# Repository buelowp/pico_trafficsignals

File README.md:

# Pi Pico Traffic Signals

Imitate road traffic signals for common anode RYB traffic signals used in model railroads.

This is a common anode solution and includes the PCB design in Eagle.

To build and run this, see the SDK instructions

https://github.com/raspberrypi/pico-sdk

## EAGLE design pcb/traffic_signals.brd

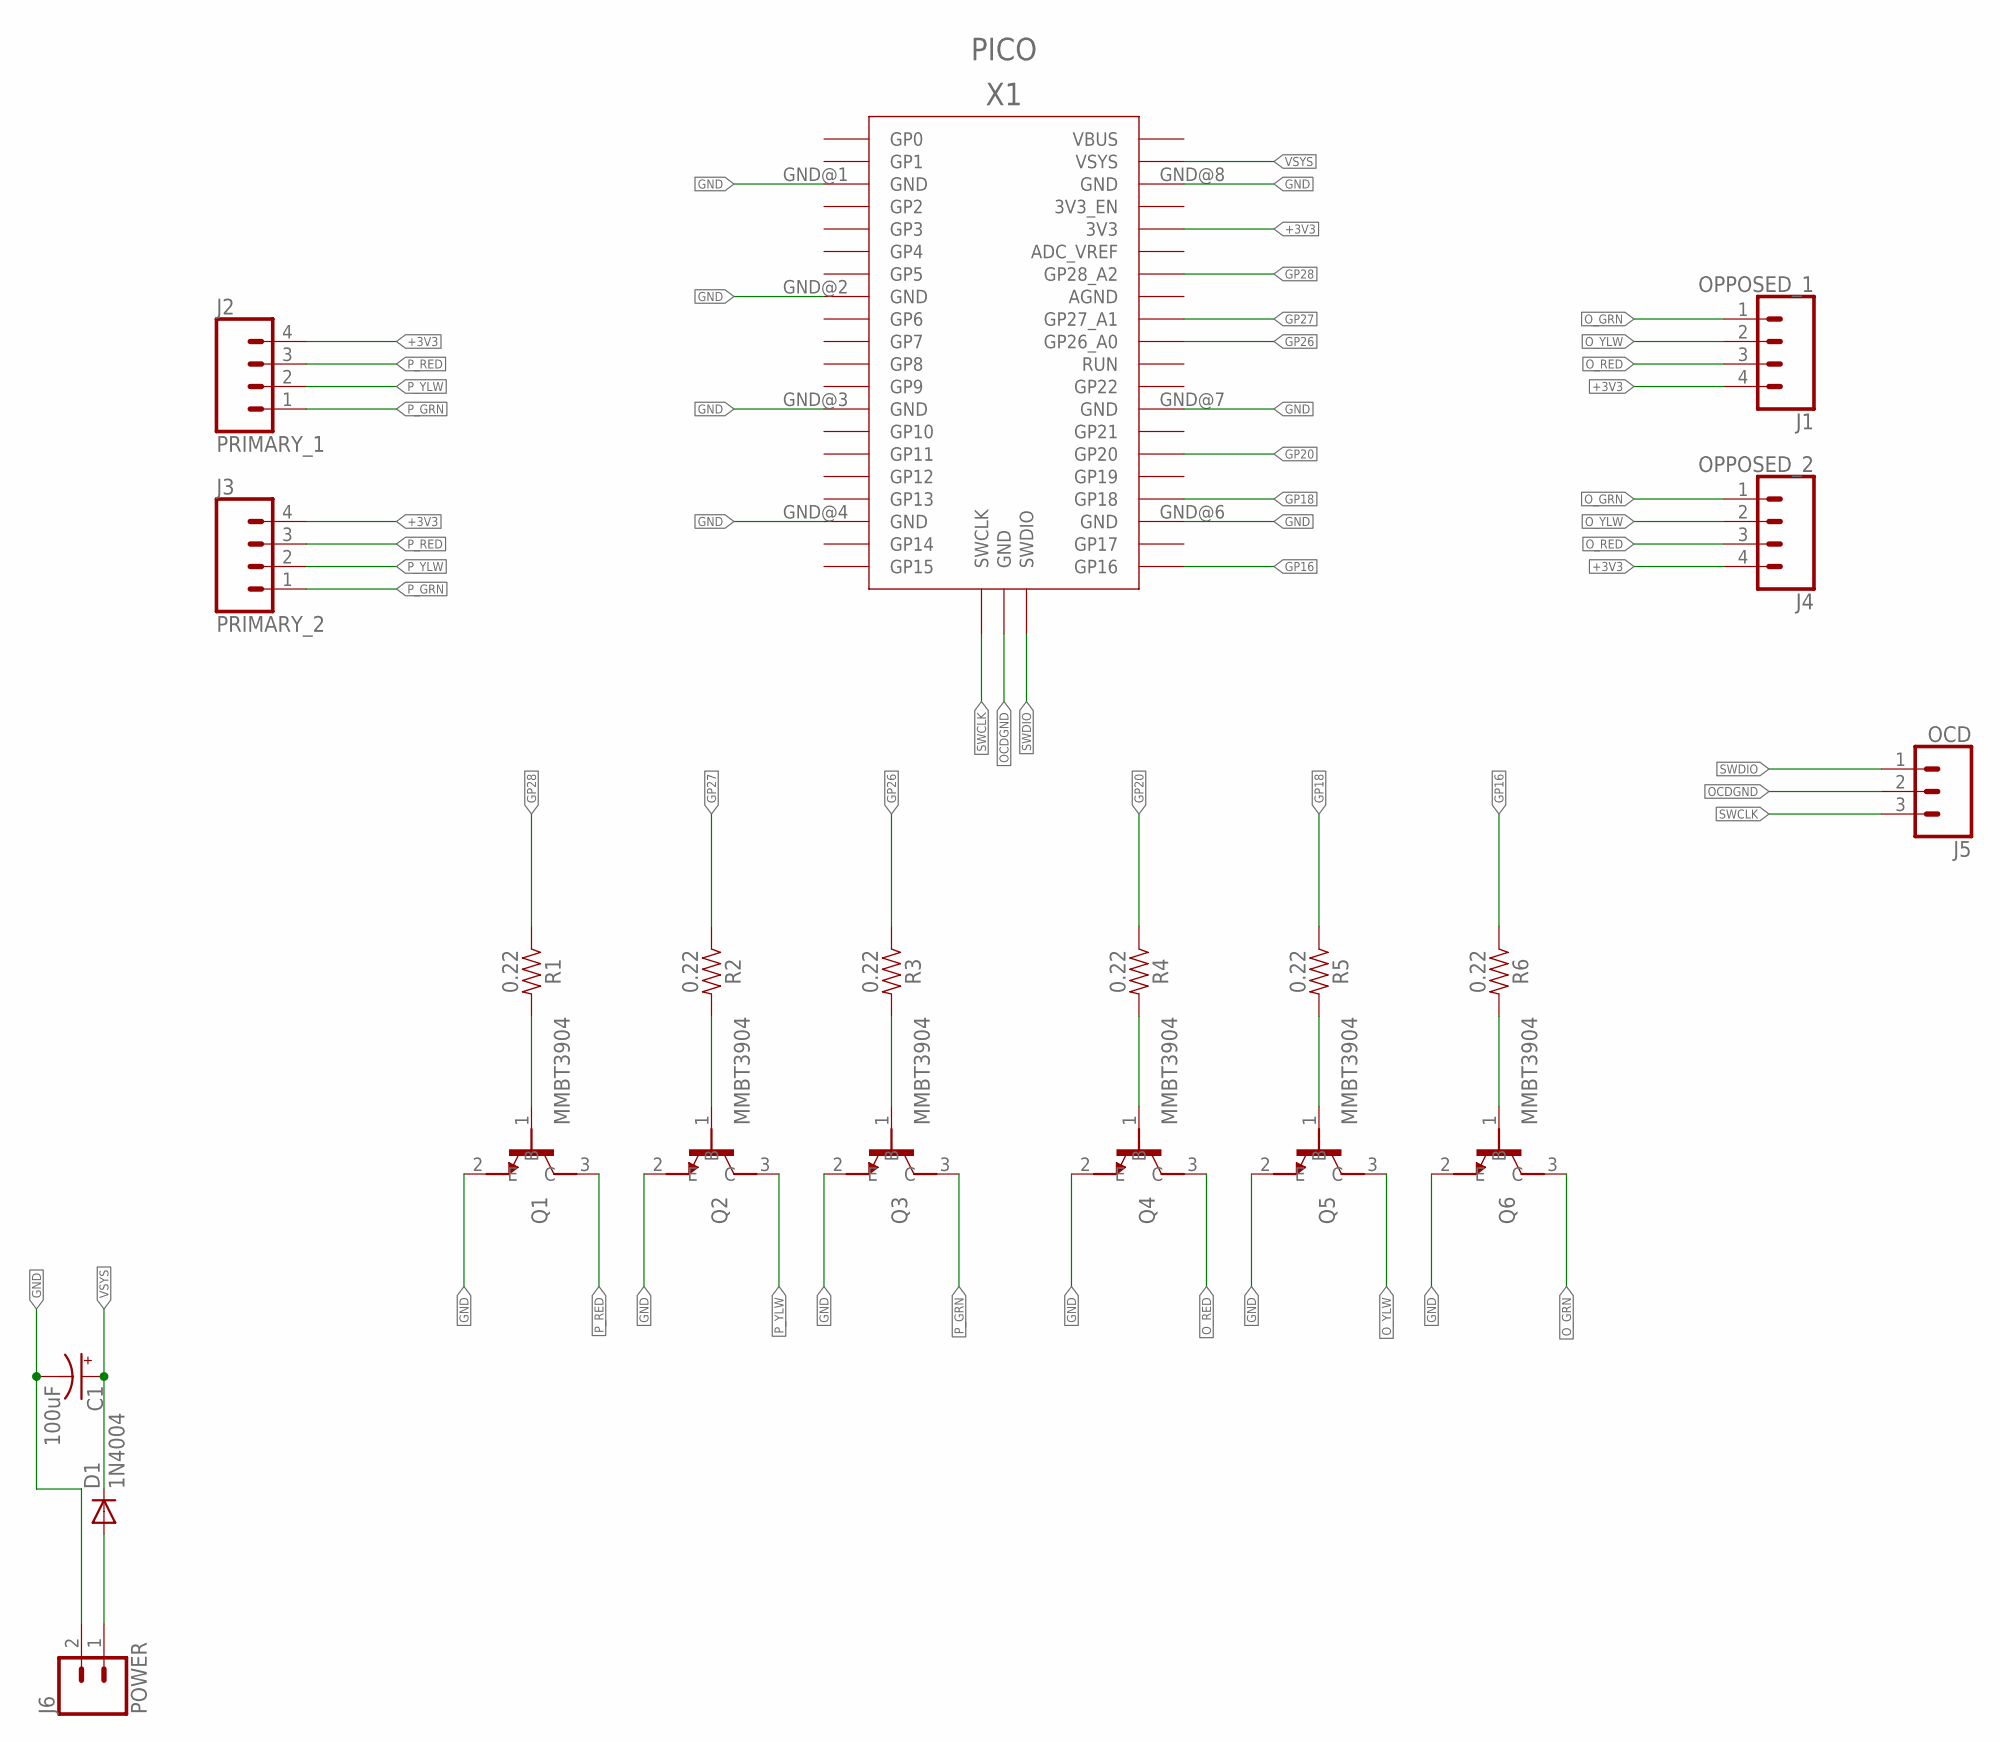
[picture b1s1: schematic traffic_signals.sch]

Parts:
C1: 100uF; CPOL-RADIAL-2.5MM-6.5MM
D1: 1N4004; DO41-10
J1: OPPOSED_1; 1X04
J2: PRIMARY_1; 1X04
J3: PRIMARY_2; 1X04
J4: OPPOSED_2; 1X04
J5: OCD; 1X03
J6: POWER; 1X02
Q1, Q2, Q3, Q4, Q5, Q6: MMBT3904; SOT95P240X120-3N
R1, R2, R3, R4, R5, R6: 0.22; 0805
X1: PICO; RPI_PICO_TH

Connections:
+3V3: J1.4, J2.4, J3.4, J4.4, X1.3V3
GND: C1.2 (-), J6.2, Q1.2 (E), Q2.2 (E), Q3.2 (E), Q4.2 (E), Q5.2 (E), Q6.2 (E), X1.GND@1 (GND), X1.GND@2 (GND), X1.GND@3 (GND), X1.GND@4 (GND), X1.GND@6 (GND), X1.GND@7 (GND), X1.GND@8 (GND)
GP16: R6.1, X1.GP16
GP18: R5.1, X1.GP18
GP20: R4.1, X1.GP20
GP26: R3.1, X1.GP26_A0
GP27: R2.1, X1.GP27_A1
GP28: R1.1, X1.GP28_A2
unnamed: D1.A, J6.1
unnamed: Q1.1 (B), R1.2
unnamed: Q2.1 (B), R2.2
unnamed: Q3.1 (B), R3.2
unnamed: Q4.1 (B), R4.2
unnamed: Q5.1 (B), R5.2
unnamed: Q6.1 (B), R6.2
OCDGND: J5.2, X1.GND@5 (GND)
O_GRN: J1.1, J4.1, Q6.3 (C)
O_RED: J1.3, J4.3, Q4.3 (C)
O_YLW: J1.2, J4.2, Q5.3 (C)
P_GRN: J2.1, J3.1, Q3.3 (C)
P_RED: J2.3, J3.3, Q1.3 (C)
P_YLW: J2.2, J3.2, Q2.3 (C)
SWCLK: J5.3, X1.SWCLK
SWDIO: J5.1, X1.SWDIO
VSYS: C1.1 (+), D1.C, X1.VSYS

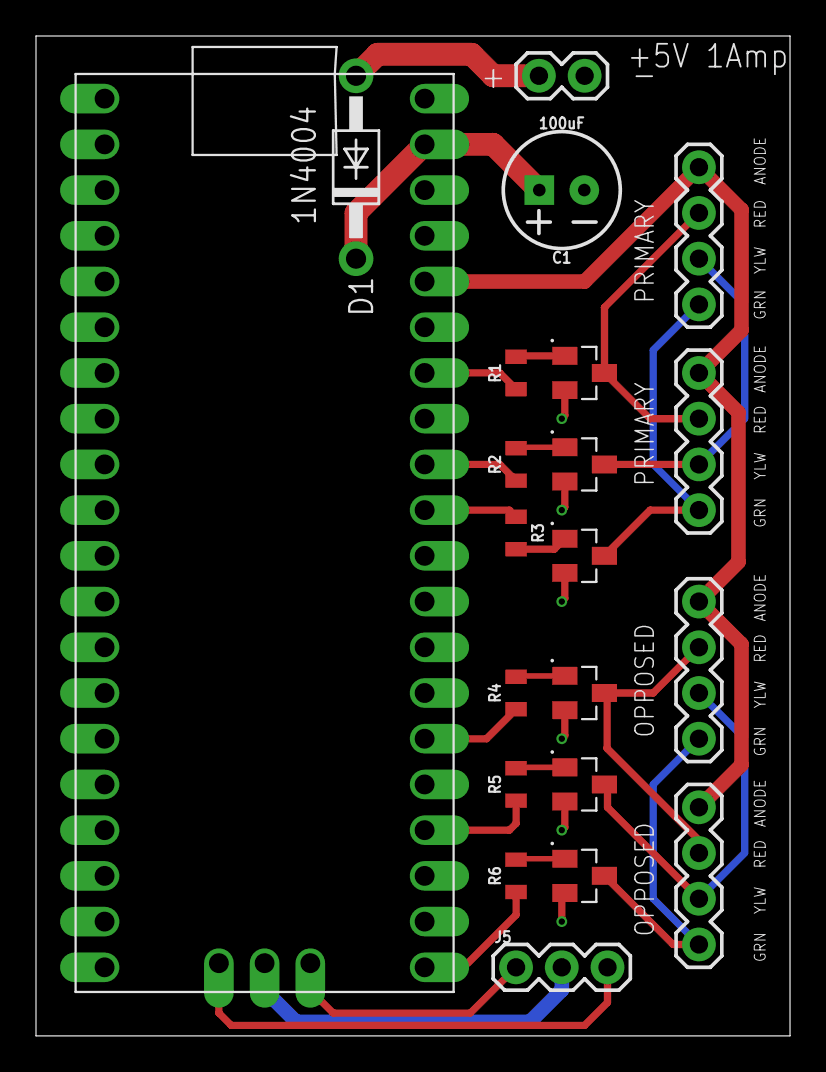
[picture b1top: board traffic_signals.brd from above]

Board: 2 copper layers, 41.9 x 55.5 mm, 21 parts (0 on the bottom side), 25 nets.

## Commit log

2021-02-22 Adding content
2021-02-22 Adding license headers
2022-08-26 Fixes and updates
    * The Adafruit pico board has different PIN numbering than the silkscreen
    * Tweak the timing a bit
    * Update the readme

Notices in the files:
parts and their libraries:
SparkFun-Connectors: Licensing: Creative Commons ShareAlike 4.0 International - https://creativecommons.org/licenses/by-sa/4.0
